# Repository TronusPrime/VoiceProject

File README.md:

# VoiceProject
Building a compact, high quality voice modulator, where future iterations will utilize ML/AI to clean up output audio and improve effect quality

You can see the code for this project in the VoiceProjectCode folder. The latest iteration of the code is SoftPitchTest3.

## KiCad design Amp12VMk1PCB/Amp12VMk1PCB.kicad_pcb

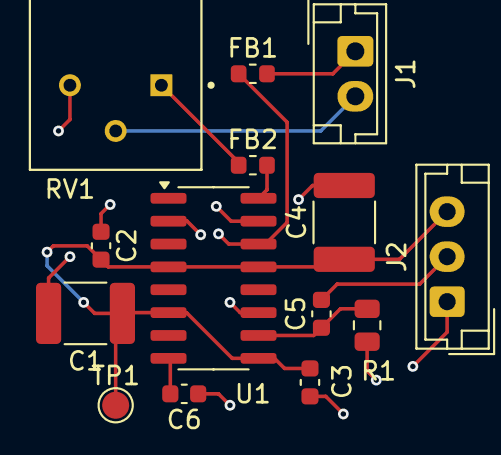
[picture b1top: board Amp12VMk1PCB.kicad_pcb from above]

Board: 2 copper layers, 14 parts (0 on the bottom side), 10 nets.

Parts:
C1, C4: 20uF; C_1812_4532Metric
C2, C3, C6: 1uF; C_0603_1608Metric
C5: 0.1uF; C_0603_1608Metric
FB1, FB2: FerriteBead; L_0603_1608Metric
J1: Conn_01x02_Socket; JST_EH_B2B-EH-A_1x02_P2.50mm_Vertical
J2: Conn_01x03_Socket; JST_EH_B3B-EH-A_1x03_P2.50mm_Vertical
R1: 10k; R_0805_2012Metric
RV1: 10k; POT_3310P-025-103L
TP1: TestPoint; TestPoint_Pad_D1.5mm
U1: PAM8406D; SOP-16_3.9x9.9mm_P1.27mm

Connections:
+5V: C1.1, C2.2, C3.2, C4.1, J2.3, TP1.1, U1.4 (PVDDL), U1.6 (VDD), U1.9 (MODE), U1.13 (PVDDR)
/inR: C5.2, J2.2
GND: C1.2, C2.1, C3.1, C4.2, C6.1, J2.1, R1.1, RV1.3, U1.2 (PGNDL), U1.11 (GND), U1.15 (PGNDR)
unnamed: FB2.1, RV1.1
unnamed: FB1.2, J1.1
unnamed: J1.2, RV1.2
unnamed: FB2.2, U1.16 (+OUT_R)
unnamed: FB1.1, U1.14 (-OUT_R)
unnamed: C5.1, R1.2, U1.10 (INR)
unnamed: C6.2, U1.8 (VREF)

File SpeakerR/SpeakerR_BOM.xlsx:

Reference | Value | Datasheet | Footprint | Qty | LCSC
C1,C4 | 20uF | ~ | Capacitor_SMD:C_1812_4532Metric | 2.0 | C76690
C2,C3,C6 | 1uF | ~ | Capacitor_SMD:C_0402_1005Metric | 3.0 | C52923
C5 | 0.1uF | ~ | Capacitor_SMD:C_0402_1005Metric | 1.0 | C1581
FB1,FB2 | FerriteBead | ~ | Inductor_SMD:L_0603_1608Metric | 2.0 | C1002
J1 | Conn_01x02_Socket | ~ | easyeda2kicad:CONN-TH_B2B-XH-A-LF-SN | 1.0 | C158012
J2 | Conn_01x03_Socket | ~ | easyeda2kicad:CONN-TH_3P-P2.50_B3B-XH-AM-LF-SN | 1.0 | C161870
R1 | 10k | ~ | Resistor_SMD:0405_1005Metric | 1.0 | C25531
RV1 | 10k |  | Potentiometer | 1.0
U1 | PAM8406D | https://www.diodes.com/assets/Datasheets/PAM8406.pdf | Package_SO:SOP-16_3.9x9.9mm_P1.27mm | 1.0 | C86270

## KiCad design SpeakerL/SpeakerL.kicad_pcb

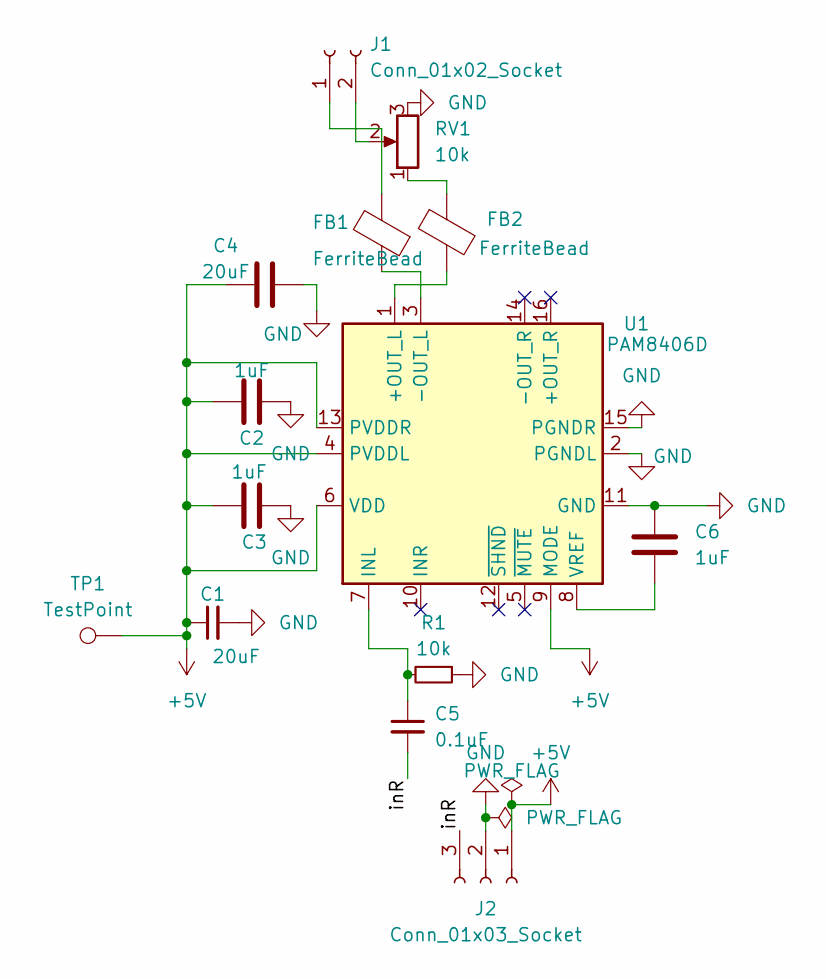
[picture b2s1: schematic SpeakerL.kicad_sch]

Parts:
C1, C4: 20uF; C_1812_4532Metric
C2, C3, C6: 1uF; C_0402_1005Metric
C5: 0.1uF; C_0402_1005Metric
FB1, FB2: FerriteBead; L_0603_1608Metric
J1: Conn_01x02_Socket; CONN-TH_B2B-XH-A-LF-SN
J2: Conn_01x03_Socket; CONN-TH_3P-P2.50_B3B-XH-AM-LF-SN
R1: 10k; R_0402_1005Metric
RV1: 10k; POT_3310P-025-103L
TP1: TestPoint; TestPoint_Pad_D1.5mm
U1: PAM8406D; SOP-16_3.9x9.9mm_P1.27mm

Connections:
+5V: C1.1, C2.2, C3.2, C4.1, J2.1, TP1.1, U1.4 (PVDDL), U1.6 (VDD), U1.9 (MODE), U1.13 (PVDDR)
/inR: C5.2, J2.3
GND: C1.2, C2.1, C3.1, C4.2, C6.1, J2.2, R1.1, RV1.3, U1.2 (PGNDL), U1.11 (GND), U1.15 (PGNDR)
unnamed: FB2.1, RV1.1
unnamed: FB1.2, J1.1
unnamed: J1.2, RV1.2
unnamed: FB2.2, U1.1 (+OUT_L)
unnamed: FB1.1, U1.3 (-OUT_L)
unnamed: C5.1, R1.2, U1.7 (INL)
unnamed: C6.2, U1.8 (VREF)

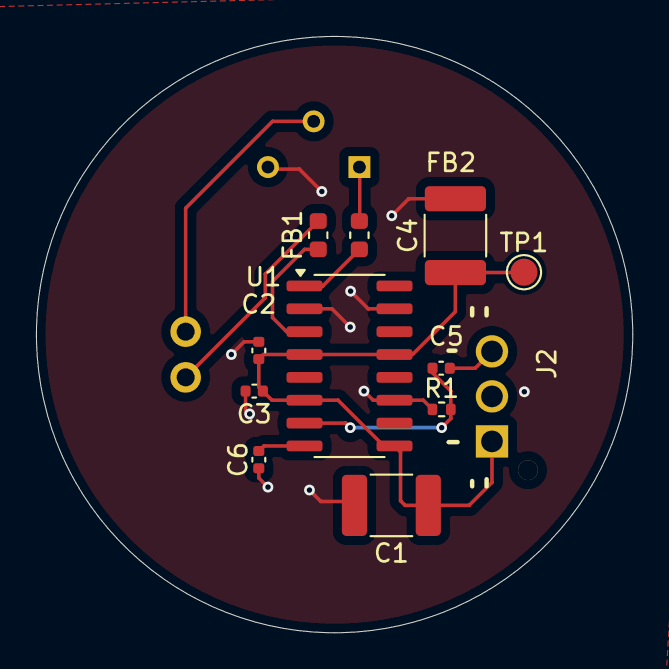
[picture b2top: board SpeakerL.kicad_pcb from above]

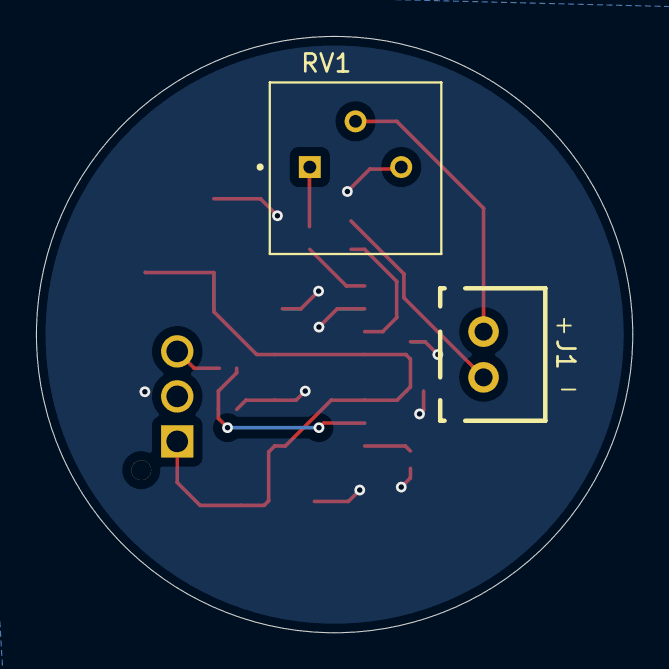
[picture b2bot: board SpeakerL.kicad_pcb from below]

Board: 2 copper layers, 33.1 x 33.1 mm, 14 parts (2 on the bottom side), 10 nets.

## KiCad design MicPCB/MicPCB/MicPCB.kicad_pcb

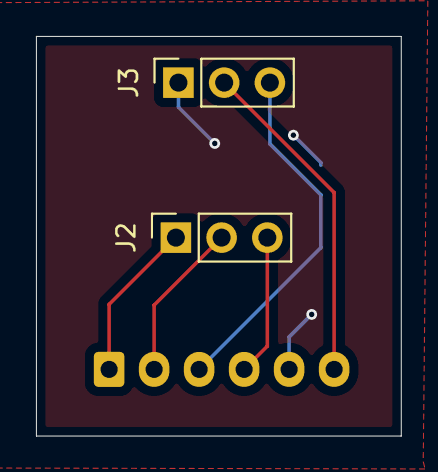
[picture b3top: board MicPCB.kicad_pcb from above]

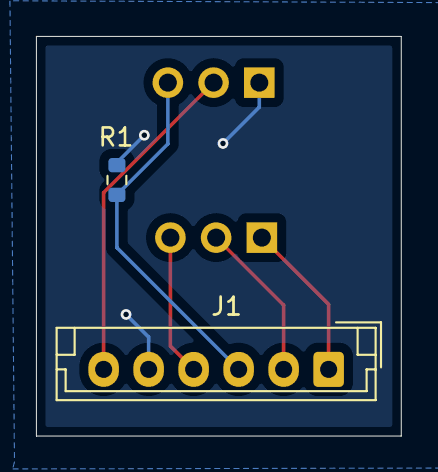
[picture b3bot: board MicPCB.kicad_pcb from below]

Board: 2 copper layers, 20.3 x 22.2 mm, 4 parts (2 on the bottom side), 6 nets.

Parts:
J1: 3.3 sel; JST_EH_B6B-EH-A_1x06_P2.50mm_Vertical
J2, J3: Conn_01x03_Socket; PinSocket_1x03_P2.54mm_Vertical
R1: 10k; R_0603_1608Metric

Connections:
+3.3V: J1.6, J3.2
/bclk: J1.4, J2.3
/lrcl: J1.2, J2.2
/sd: J1.3, J3.3, R1.1
/sel: J1.1, J2.1
GND: J1.5, J3.1, R1.2

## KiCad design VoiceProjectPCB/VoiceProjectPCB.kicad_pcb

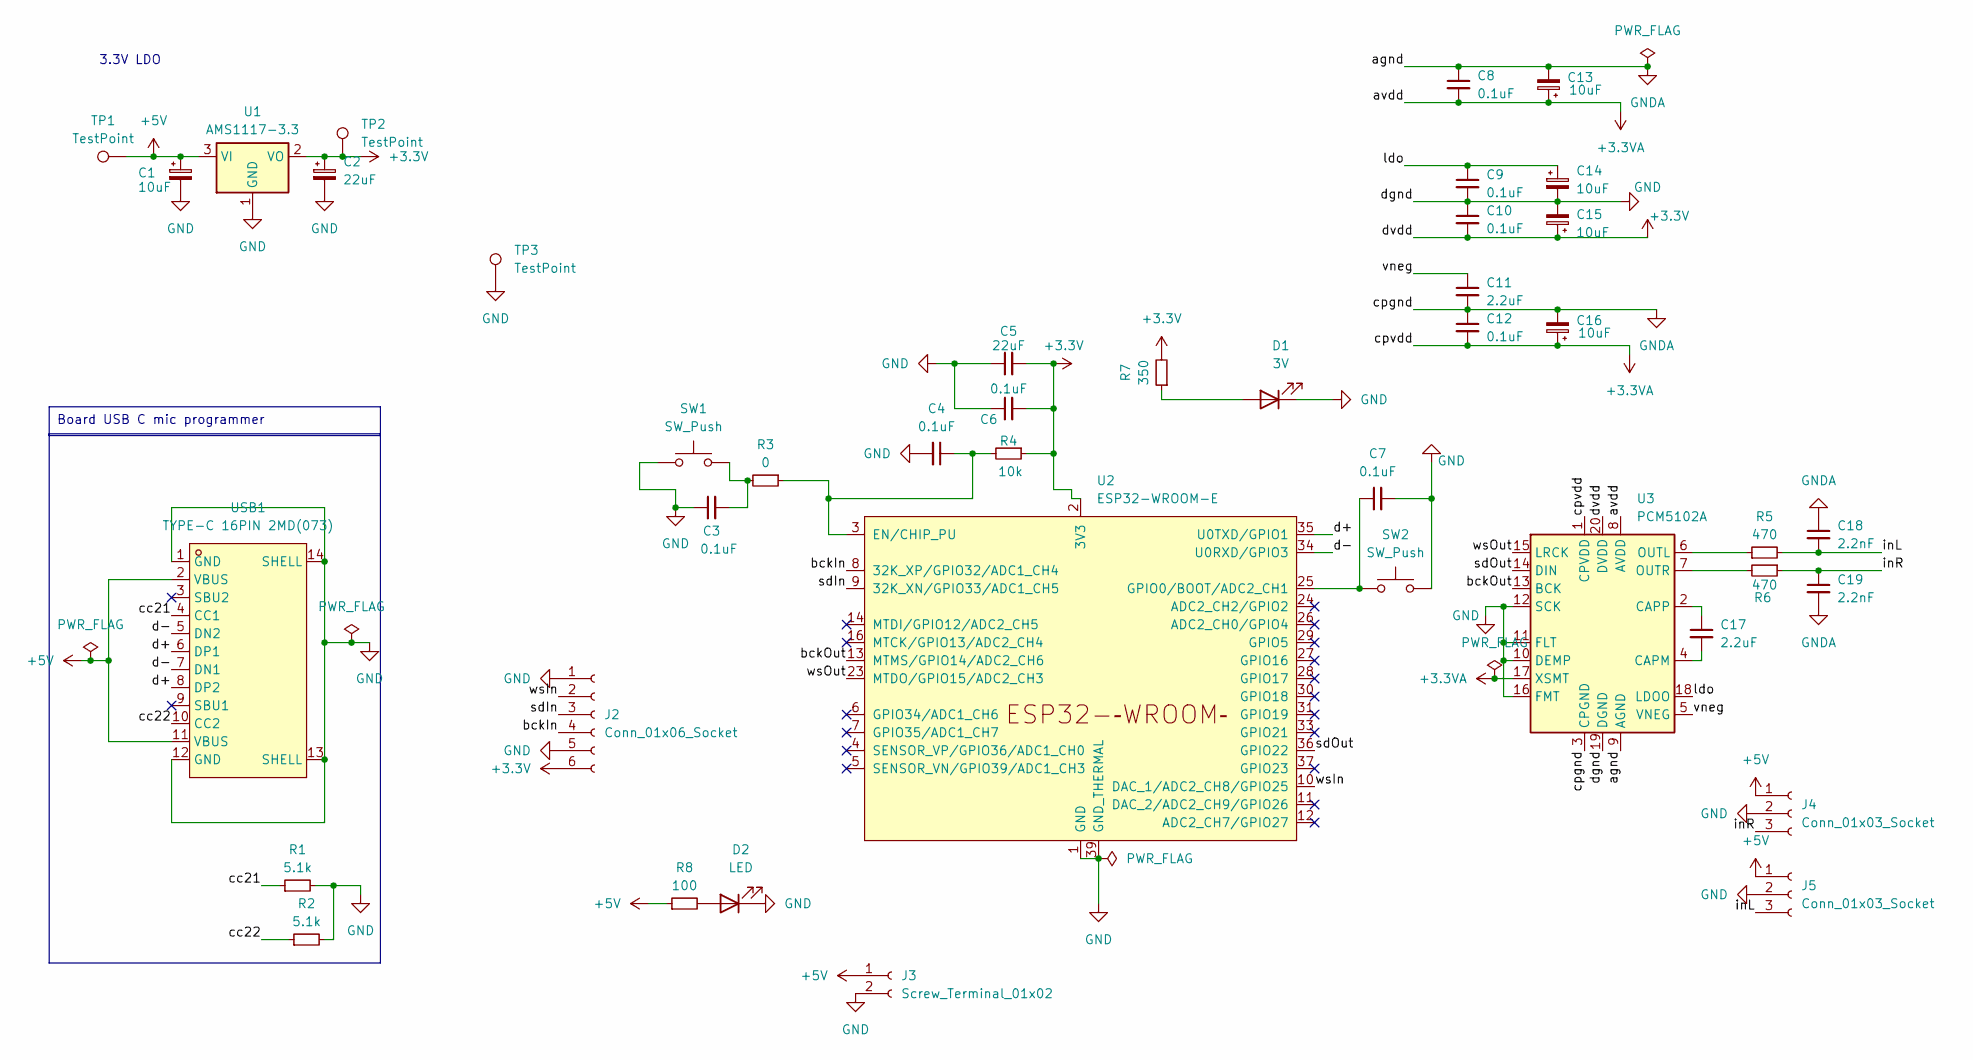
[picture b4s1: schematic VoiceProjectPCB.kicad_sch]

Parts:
C1, C13, C14, C15, C16: 10uF; C_0402_1005Metric
C2: 22uF; C_0402_1005Metric
C3, C4, C7, C8, C9, C10, C12: 0.1uF; C_0402_1005Metric
C5: 22uF; C_0805_2012Metric_Pad1.18x1.45mm_HandSolder
C6: 0.1uF; C_0805_2012Metric_Pad1.18x1.45mm_HandSolder
C11: 2.2uF; C_0402_1005Metric
C17: 2.2uF; C_0805_2012Metric_Pad1.18x1.45mm_HandSolder
C18, C19: 2.2nF; C_0402_1005Metric
D1: 3V; LED_0603_1608Metric
D2: LED; LED_0603_1608Metric
J2: Conn_01x06_Socket; JST_B6B-XH-A
J3: Screw_Terminal_01x02; JST_B2B-XH-A
J4, J5: Conn_01x03_Socket; JST_B3B-XH-A
R1, R2: 5.1k; R_0402_1005Metric
R3: 0; R_0402_1005Metric
R4: 10k; R_0402_1005Metric
R5, R6: 470; R_0402_1005Metric
R7: 350; R_0402_1005Metric
R8: 100; R_0402_1005Metric
SW1, SW2: SW_Push; SW2_PTS636 SM25F SMTR LFS_CNK
TP1, TP2, TP3: TestPoint; TestPoint_Pad_D1.5mm
U1: AMS1117-3.3; SOT-223-3_TabPin2
U2: ESP32-WROOM-E; ESP32-WROOM-32E
U3: PCM5102A; TSSOP-20_4.4x6.5mm_P0.65mm
USB1: TYPE-C 16PIN 2MD(073); USB-C-SMD_TYPE-C-6PIN-2MD-073; LCSC Part C2765186

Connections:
+3.3V: C2.1, C5.2, C6.2, C10.2, C15.1, J2.6, R4.1, R7.2, TP2.1, U1.2 (VO), U2.2 (3V3), U3.20 (DVDD)
+3.3VA: C8.2, C12.2, C13.1, C16.1, U3.1 (CPVDD), U3.8 (AVDD), U3.17 (XSMT)
+5V: C1.1, J3.1, J4.1, J5.1, R8.1, TP1.1, U1.3 (VI), USB1.2 (VBUS), USB1.11 (VBUS)
/bckIn: J2.4, U2.8 (32K_XP/GPIO32/ADC1_CH4)
/bckOut: U2.13 (MTMS/GPIO14/ADC2_CH6), U3.13 (BCK)
/cc21: R1.1, USB1.4 (CC1)
/cc22: R2.1, USB1.10 (CC2)
/d+: U2.35 (U0TXD/GPIO1), USB1.6 (DP1), USB1.8 (DP2)
/d-: U2.34 (U0RXD/GPIO3), USB1.5 (DN2), USB1.7 (DN1)
/inL: C18.2, J5.3, R5.2
/inR: C19.1, J4.3, R6.1
/ldo: C9.1, C14.1, U3.18 (LDOO)
/sdIn: J2.3, U2.9 (32K_XN/GPIO33/ADC1_CH5)
/sdOut: U2.36 (GPIO22), U3.14 (DIN)
/vneg: C11.1, U3.5 (VNEG)
/wsIn: J2.2, U2.10 (DAC_1/ADC2_CH8/GPIO25)
/wsOut: U2.23 (MTDO/GPIO15/ADC2_CH3), U3.15 (LRCK)
GND: C1.2, C2.2, C3.1, C4.2, C5.1, C6.1, C7.2, C9.2, C10.1, C14.2, C15.2, D1.1 (K), D2.1 (K), J2.1, J2.5, J3.2, J4.2, J5.2, R1.2, R2.2, SW1.1, SW2.2, TP3.1, U1.1 (GND), U2.1 (GND), U2.15 (GND), U2.38 (GND), U2.39 (GND_THERMAL), U3.10 (DEMP), U3.11 (FLT), U3.12 (SCK), U3.16 (FMT), U3.19 (DGND), USB1.1 (GND), USB1.12 (GND), USB1.13 (SHELL), USB1.14 (SHELL)
GNDA: C8.1, C11.2, C12.1, C13.2, C16.2, C18.1, C19.2, U3.3 (CPGND), U3.9 (AGND)
unnamed: C3.2, R3.2, SW1.2
unnamed: D1.2 (A), R7.1
unnamed: D2.2 (A), R8.2
unnamed: C4.1, R3.1, R4.2, U2.3 (EN/CHIP_PU)
unnamed: C7.1, SW2.1, U2.25 (GPIO0/BOOT/ADC2_CH1)
unnamed: C17.2, U3.4 (CAPM)
unnamed: C17.1, U3.2 (CAPP)
unnamed: R5.1, U3.6 (OUTL)
unnamed: R6.2, U3.7 (OUTR)

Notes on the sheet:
Board USB C mic programmer
3.3V LDO

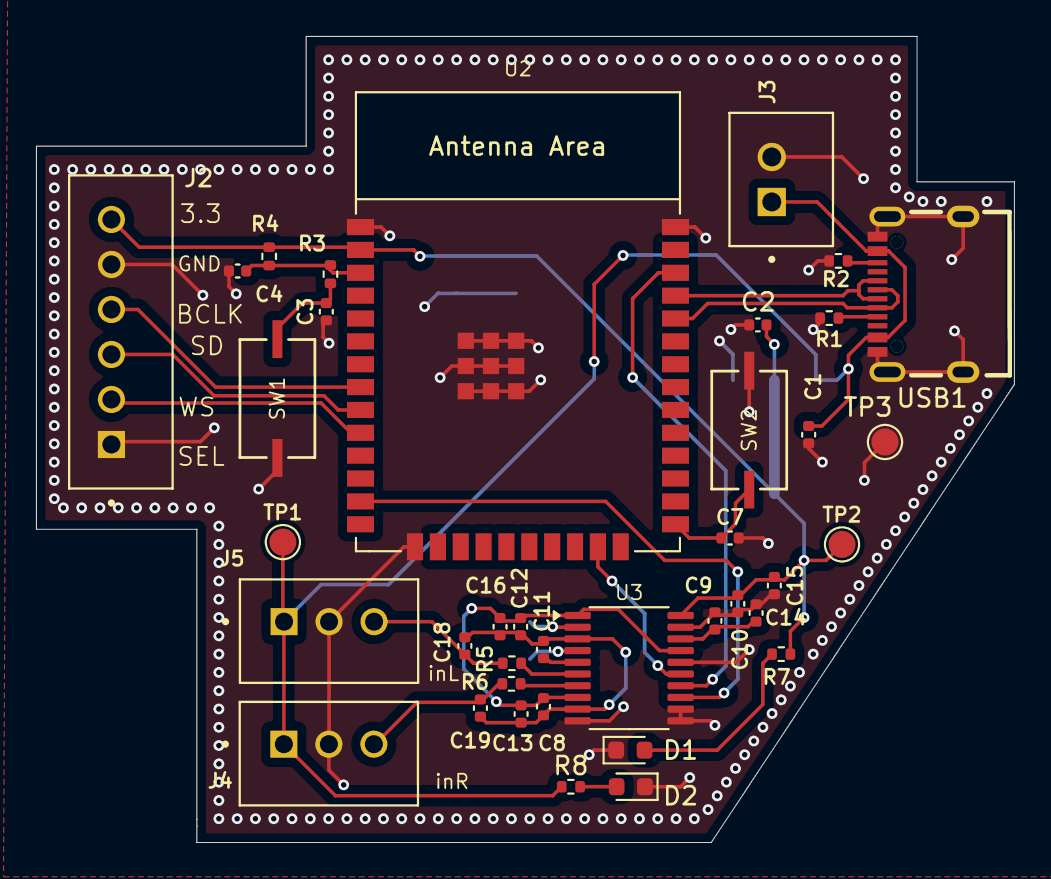
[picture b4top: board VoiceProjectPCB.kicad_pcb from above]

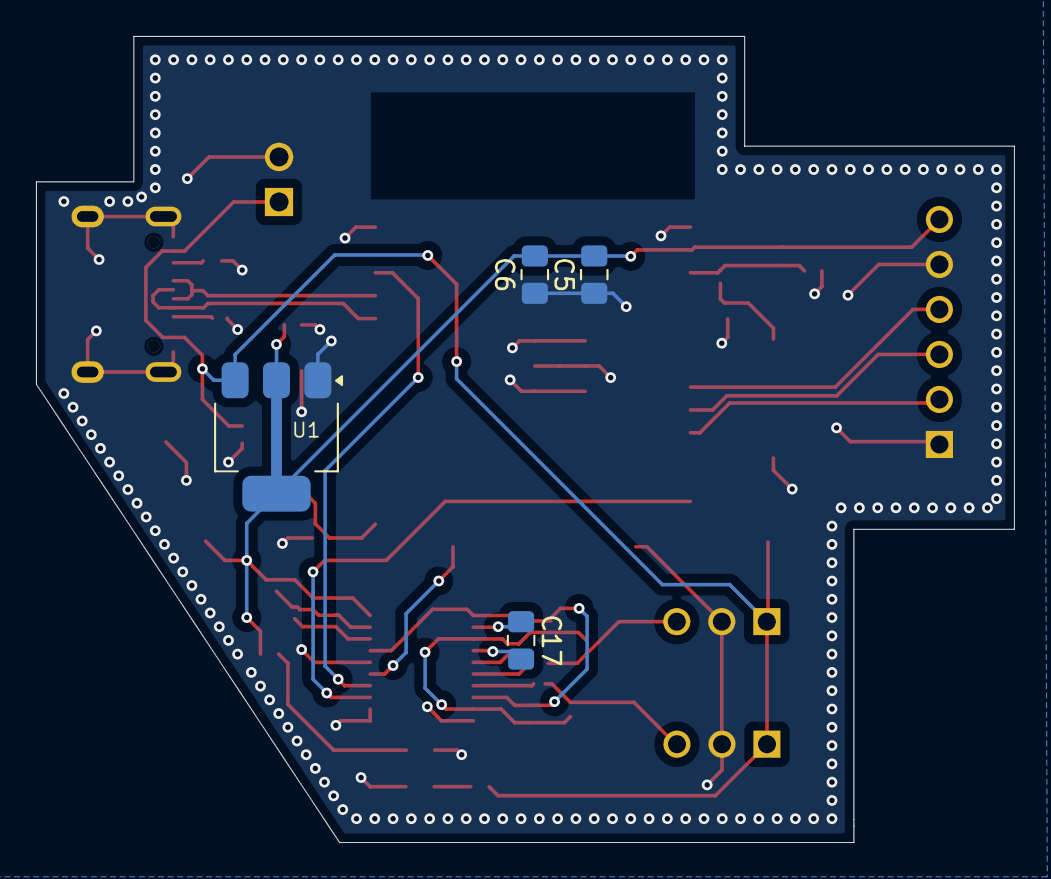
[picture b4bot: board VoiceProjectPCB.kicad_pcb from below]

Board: 2 copper layers, 54.3 x 44.8 mm, 42 parts (4 on the bottom side), 28 nets.

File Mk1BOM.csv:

"Reference","Value","Datasheet","Footprint","Qty","DNP"
"C1,C13,C14,C15,C16","10uF","~","Capacitor_SMD:C_0402_1005Metric","5",""
"C2,C5","22uF","~","-- mixed values --","2",""
"C3,C4,C6,C7,C8,C9,C10,C12","0.1uF","~","-- mixed values --","8",""
"C11,C17","2.2uF","~","-- mixed values --","2",""
"C18,C19","2.2nF","~","Capacitor_SMD:C_0402_1005Metric","2",""
"D1","3V","~","LED_SMD:LED_0603_1608Metric","1",""
"D2","LED","~","LED_SMD:LED_0603_1608Metric","1",""
"J2","Conn_01x06_Socket","~","B6B_XH_A:JST_B6B-XH-A","1",""
"J3","Screw_Terminal_01x02","~","B2B_XH_A:JST_B2B-XH-A","1",""
"J4,J5","Conn_01x03_Socket","~","B3B_XH_A:JST_B3B-XH-A","2",""
"R1,R2","5.1k","~","Resistor_SMD:R_0402_1005Metric","2",""
"R3","0","~","Resistor_SMD:R_0402_1005Metric","1",""
"R4","10k","~","Resistor_SMD:R_0402_1005Metric","1",""
"R5,R6","470","~","Resistor_SMD:R_0402_1005Metric","2",""
"R7","350","~","Resistor_SMD:R_0402_1005Metric","1",""
"R8","100","~","Resistor_SMD:R_0402_1005Metric","1",""
"SW1,SW2","SW_Push","~","Switch:SW2_PTS636 SM25F SMTR LFS_CNK","2",""
"TP1,TP2,TP3","TestPoint","~","TestPoint:TestPoint_Pad_D1.5mm","3",""
"U1","AMS1117-3.3","http://www.advanced-monolithic.com/pdf/ds1117.pdf","Package_TO_SOT_SMD:SOT-223-3_TabPin2","1",""
"U2","ESP32-WROOM-E","https://www.espressif.com/sites/default/files/documentation/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","Espressif:ESP32-WROOM-32E","1",""
"U3","PCM5102A","https://www.ti.com/lit/ds/symlink/pcm5102a.pdf","Package_SO:TSSOP-20_4.4x6.5mm_P0.65mm","1",""
"USB1","TYPE-C 16PIN 2MD(073)","","easyeda2kicad:USB-C-SMD_TYPE-C-6PIN-2MD-073","1",""

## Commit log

2024-10-29 Add files via upload
    Moved Project to Github Repo. Current Code: Mk3. Current PCB: Mk1
2024-11-20 Mk 2 PCB, Switched to DSP for Voice Modulation
